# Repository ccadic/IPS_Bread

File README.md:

# IPS_Bread
1.54" Color IPS TFT display breadboard Kicad PCB with joystick

Joystick: https://www.aliexpress.com/item/5pcs-free-shipping-7mm-x-7mm-6-Pin-5-Way-Momentary-Pushbutton-PCB-SMD-SMT-Tactile/32902822257.html
IPS Display: https://www.aliexpress.com/item/New-IPS-1-3-inch-3-3V-12PIN-SPI-HD-Full-Color-TFT-Display-Screen-ST7789/32859374478.html

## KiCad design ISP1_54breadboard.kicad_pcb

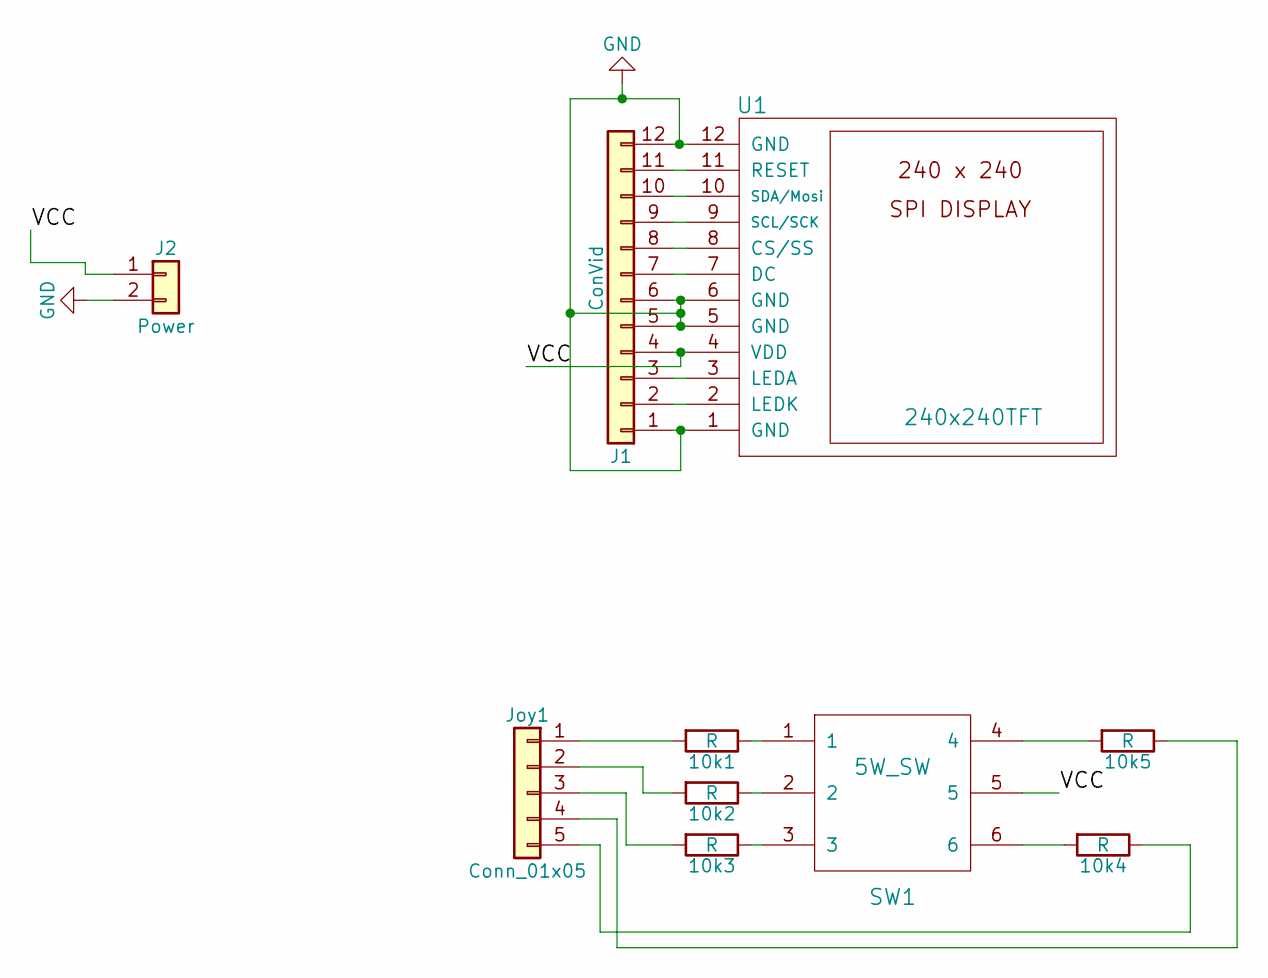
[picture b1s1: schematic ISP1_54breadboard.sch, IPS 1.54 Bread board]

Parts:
10k1, 10k2, 10k3, 10k4, 10k5: R; R_1206_HandSoldering
J1: ConVid; Socket_Strip_Straight_1x12_Pitch2.54mm
J2: Power; Socket_Strip_Straight_1x02_Pitch2.54mm
Joy1: Conn_01x05; Socket_Strip_Straight_1x05_Pitch2.54mm
SW1: 5W_SW; 5WAY_sw
U1: 240x240TFT; 240240TFT

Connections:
/VCC: J1.4, J2.1, SW1.5, U1.4 (VDD)
GND: J1.1, J1.5, J1.6, J1.12, J2.2, U1.1 (GND), U1.5 (GND), U1.6 (GND), U1.12 (GND)
unnamed: 10k1.1, SW1.1
unnamed: 10k1.2, Joy1.1
unnamed: 10k2.1, SW1.2
unnamed: 10k2.2, Joy1.2
unnamed: 10k3.1, SW1.3
unnamed: 10k3.2, Joy1.3
unnamed: 10k4.1, Joy1.5
unnamed: 10k4.2, SW1.6
unnamed: 10k5.1, Joy1.4
unnamed: 10k5.2, SW1.4
unnamed: J1.2, U1.2 (LEDK)
unnamed: J1.3, U1.3 (LEDA)
unnamed: J1.7, U1.7 (DC)
unnamed: J1.8, U1.8 (CS/SS)
unnamed: J1.9, U1.9 (SCL/SCK)
unnamed: J1.10, U1.10 (SDA/Mosi)
unnamed: J1.11, U1.11 (RESET)

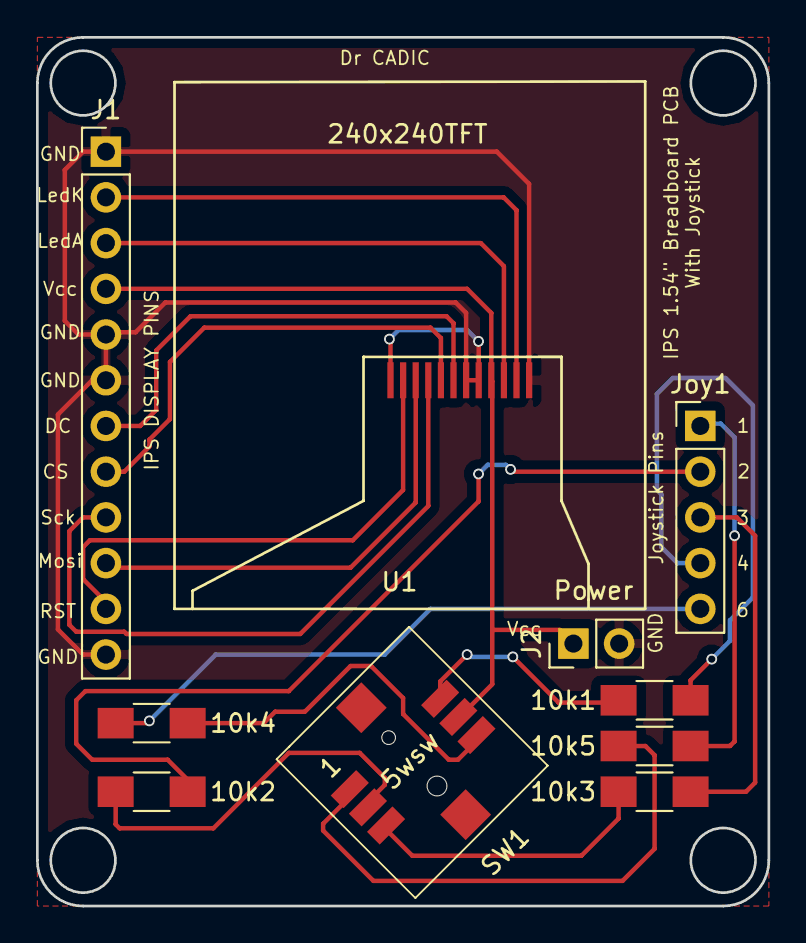
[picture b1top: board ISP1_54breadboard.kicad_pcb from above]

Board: 2 copper layers, 40.6 x 48.3 mm, 10 parts (0 on the bottom side), 19 nets.
